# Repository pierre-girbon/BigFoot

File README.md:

Big Foot
=========
Foot switch midi controller

Features
--------

    1. 8 assignable footswitches
    2. Bank selection
    3. 2 expression pedals connectors with TRS/RTS switch
    4. USB Midi input and output
    5. Midi DIN output
    6. (TODO) LED feedback

Presets Setup
-------------
Preset must be defined into a '.h' file in the Firmware/include folder, then included into Firmware/src/main.cpp file (see RolandMC707.h file as example) and compiled.

See [Control Surface](https://github.com/tttapa/Control-Surface) library for possible presets.

Building
--------

Folder structure:

- PCB: KiCAD schematics and PCB
    - Gerber: gerger files to order PCB production
    - [Mouser part list](https://www.mouser.fr/ProjectManager/ProjectDetail.aspx?AccessID=45c124cc8a)
- Enclosure: KiCAD files for the top panel
- Firware: source code

Compiling source code requires [platformio](https://docs.platformio.org/en/latest/)

Licence
-------
[CC BY-NC 4.0](https://creativecommons.org/licenses/by-nc/4.0/)

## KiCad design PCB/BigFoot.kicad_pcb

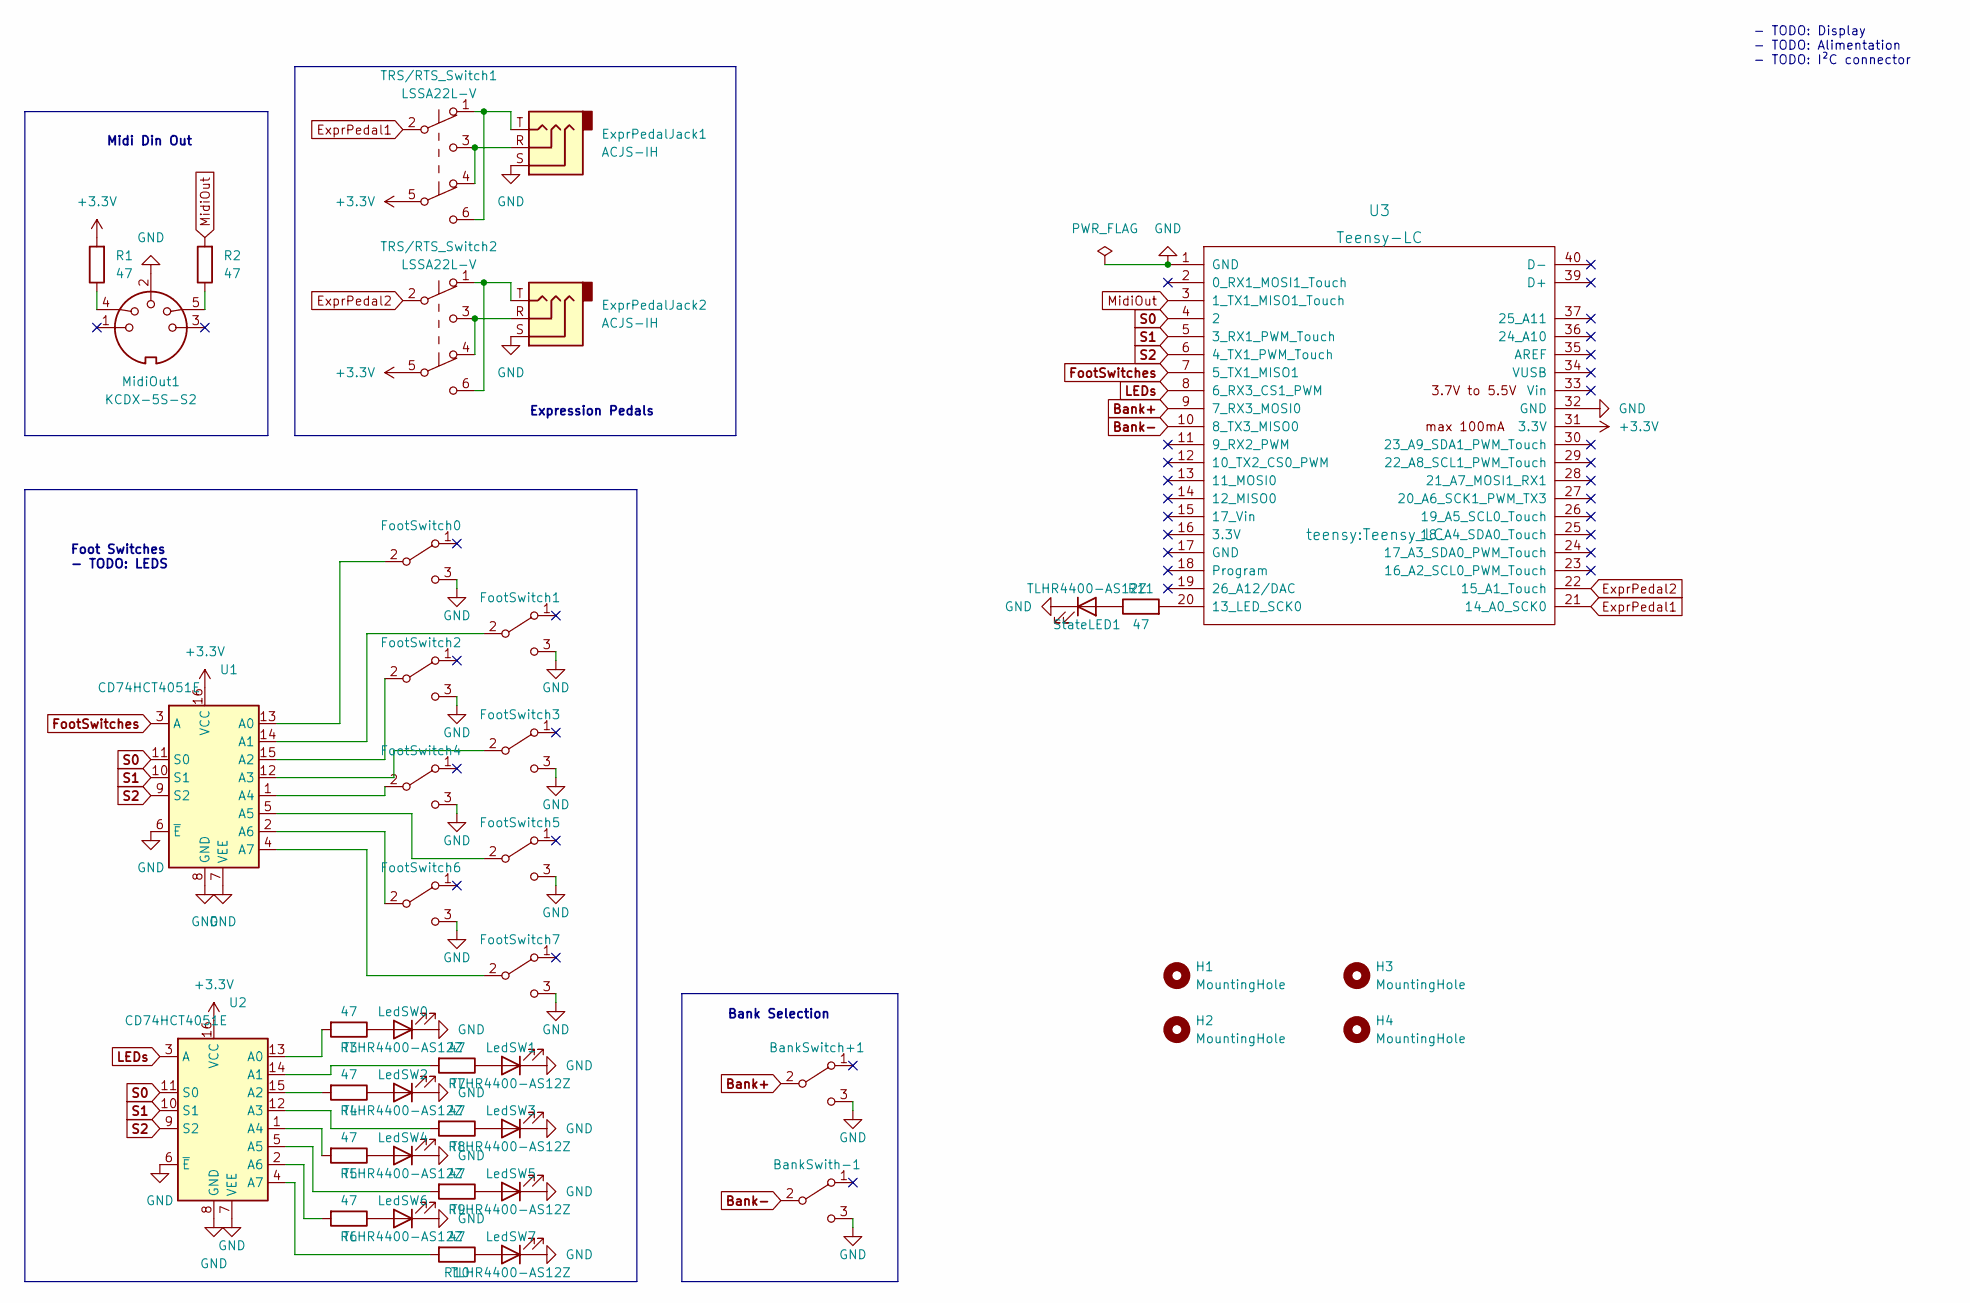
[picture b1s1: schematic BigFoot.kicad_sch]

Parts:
BankSwitch+1: FS5700SPMT2B2M1QEH; Switch_Foot_SPDT_Momentary_Eswitch_FS5700SPMT2B2M1QEH
BankSwith-1: FS5700SPMT2B2M1QEH; Switch_Foot_SPDT_Momentary_Eswitch_FS5700SPMT2B2M1QEH
ExprPedalJack1, ExprPedalJack2: ACJS-IH; Jack_6.35_Horizontal_Amphenol_ACJS-IH
FootSwitch0, FootSwitch1, FootSwitch2, FootSwitch3, FootSwitch4, FootSwitch5, FootSwitch6, FootSwitch7: FS5700SPMT2B2M1QEH; Switch_Foot_SPDT_Momentary_Eswitch_FS5700SPMT2B2M1QEH
H1, H2, H3, H4: MountingHole; MountingHole_3.2mm_M3
LedSW0, LedSW1, LedSW2, LedSW3, LedSW4, LedSW5, LedSW6, LedSW7: TLHR4400-AS12Z; LED_D3.0mm
MidiOut1: KCDX-5S-S2; Circular_DIN_5P_KCDX-5S-S2
R1, R2, R3, R4, R5, R6, R7, R8, R9, R10, R11: 47; R_Axial_DIN0309_L9.0mm_D3.2mm_P15.24mm_Horizontal
StateLED1: TLHR4400-AS12Z; LED_D3.0mm
TRS/RTS_Switch1, TRS/RTS_Switch2: LSSA22L-V; Switch_slide_2PDT_LSSA22L-V
U1, U2: CD74HCT4051E; DIP-16_W7.62mm
U3: Teensy-LC; Teensy_LC

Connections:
+3.3V: R1.2, TRS/RTS_Switch1.5 (B), TRS/RTS_Switch2.5 (B), U1.16 (VCC), U2.16 (VCC), U3.31 (3.3V)
Bank+: BankSwitch+1.2 (B), U3.9 (7_RX3_MOSI0)
Bank-: BankSwith-1.2 (B), U3.10 (8_TX3_MISO0)
ExprPedal1: TRS/RTS_Switch1.2 (B), U3.21 (14_A0_SCK0)
ExprPedal2: TRS/RTS_Switch2.2 (B), U3.22 (15_A1_Touch)
FootSwitches: U1.3 (A), U3.7 (5_TX1_MISO1)
GND: BankSwitch+1.3 (C), BankSwith-1.3 (C), ExprPedalJack1.S, ExprPedalJack2.S, FootSwitch0.3 (C), FootSwitch1.3 (C), FootSwitch2.3 (C), FootSwitch3.3 (C), FootSwitch4.3 (C), FootSwitch5.3 (C), FootSwitch6.3 (C), FootSwitch7.3 (C), LedSW0.1 (K), LedSW1.1 (K), LedSW2.1 (K), LedSW3.1 (K), LedSW4.1 (K), LedSW5.1 (K), LedSW6.1 (K), LedSW7.1 (K), MidiOut1.2, StateLED1.1 (K), U1.6 (~E), U1.7 (VEE), U1.8 (GND), U2.6 (~E), U2.7 (VEE), U2.8 (GND), U3.1 (GND), U3.32 (GND)
LEDs: U2.3 (A), U3.8 (6_RX3_CS1_PWM)
MidiOut: R2.2, U3.3 (1_TX1_MISO1_Touch)
unnamed: ExprPedalJack1.R, TRS/RTS_Switch1.3 (C), TRS/RTS_Switch1.4 (A)
unnamed: ExprPedalJack1.T, TRS/RTS_Switch1.1 (A), TRS/RTS_Switch1.6 (C)
unnamed: ExprPedalJack2.R, TRS/RTS_Switch2.3 (C), TRS/RTS_Switch2.4 (A)
unnamed: ExprPedalJack2.T, TRS/RTS_Switch2.1 (A), TRS/RTS_Switch2.6 (C)
unnamed: FootSwitch0.2 (B), U1.13 (A0)
unnamed: FootSwitch1.2 (B), U1.14 (A1)
unnamed: FootSwitch2.2 (B), U1.15 (A2)
unnamed: FootSwitch3.2 (B), U1.12 (A3)
unnamed: FootSwitch4.2 (B), U1.1 (A4)
unnamed: FootSwitch5.2 (B), U1.5 (A5)
unnamed: FootSwitch6.2 (B), U1.2 (A6)
unnamed: FootSwitch7.2 (B), U1.4 (A7)
unnamed: LedSW0.2 (A), R3.1
unnamed: LedSW1.2 (A), R7.1
unnamed: LedSW2.2 (A), R4.1
unnamed: LedSW3.2 (A), R8.1
unnamed: LedSW4.2 (A), R5.1
unnamed: LedSW5.2 (A), R9.1
unnamed: LedSW6.2 (A), R6.1
unnamed: LedSW7.2 (A), R10.1
unnamed: MidiOut1.4, R1.1
unnamed: MidiOut1.5, R2.1
unnamed: R3.2, U2.13 (A0)
unnamed: R4.2, U2.15 (A2)
unnamed: R5.2, U2.1 (A4)
unnamed: R6.2, U2.2 (A6)
unnamed: R7.2, U2.14 (A1)
unnamed: R8.2, U2.12 (A3)
unnamed: R9.2, U2.5 (A5)
unnamed: R10.2, U2.4 (A7)
unnamed: R11.2, U3.20 (13_LED_SCK0)
unnamed: R11.1, StateLED1.2 (A)
S0: U1.11 (S0), U2.11 (S0), U3.4 (2)
S1: U1.10 (S1), U2.10 (S1), U3.5 (3_RX1_PWM_Touch)
S2: U1.9 (S2), U2.9 (S2), U3.6 (4_TX1_PWM_Touch)

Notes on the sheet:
Foot Switches - TODO: LEDS
Expression Pedals
- TODO: Display - TODO: Alimentation - TODO: I²C connector
Bank Selection
Midi Din Out

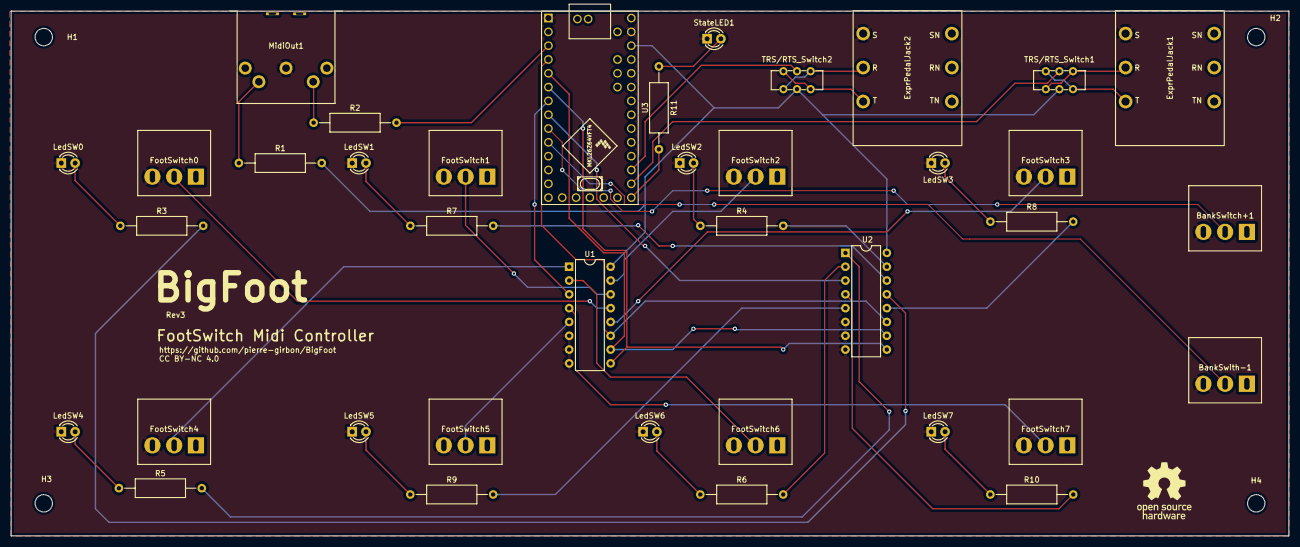
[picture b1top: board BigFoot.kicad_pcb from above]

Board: 2 copper layers, 235.0 x 96.5 mm, 42 parts (0 on the bottom side), 44 nets.

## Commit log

2022-12-12 Final PCB Version
2022-12-12 Panel PCB
2022-12-21 Minor changes on PCB
2022-12-22 Initial Firmware Commit
2022-12-23 Implementation with Control Surface
2022-12-23 Initial implementation of bank management
2022-12-24 Roalnd MC 707 setup
2022-12-24 Separated config file from main file
2022-12-27 Pre Release version
2022-12-27 Version 3.0
2022-12-27 USB name
2023-01-02 Initial KorgD1 setup (not working)
2023-08-20 Enclosure modif
2023-08-20 plateformio.ini modif on Control Surface version
